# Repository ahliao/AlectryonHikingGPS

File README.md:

Trail Utility Tool

For basic GPS functions when hiking in the middle of nowhere.
Uses a microprocessor for handling GPS data and displaying them to a LCD screen. 

Intended Features:
- Geolocation of module on a geo-image 
- Waypoint management
- Portable battery life of 12 hours
- Rechargable with solar cells
- Rugged package for rough terrain

Possible add-ons:
- Bluetooth support for data recording (or just a SD card)

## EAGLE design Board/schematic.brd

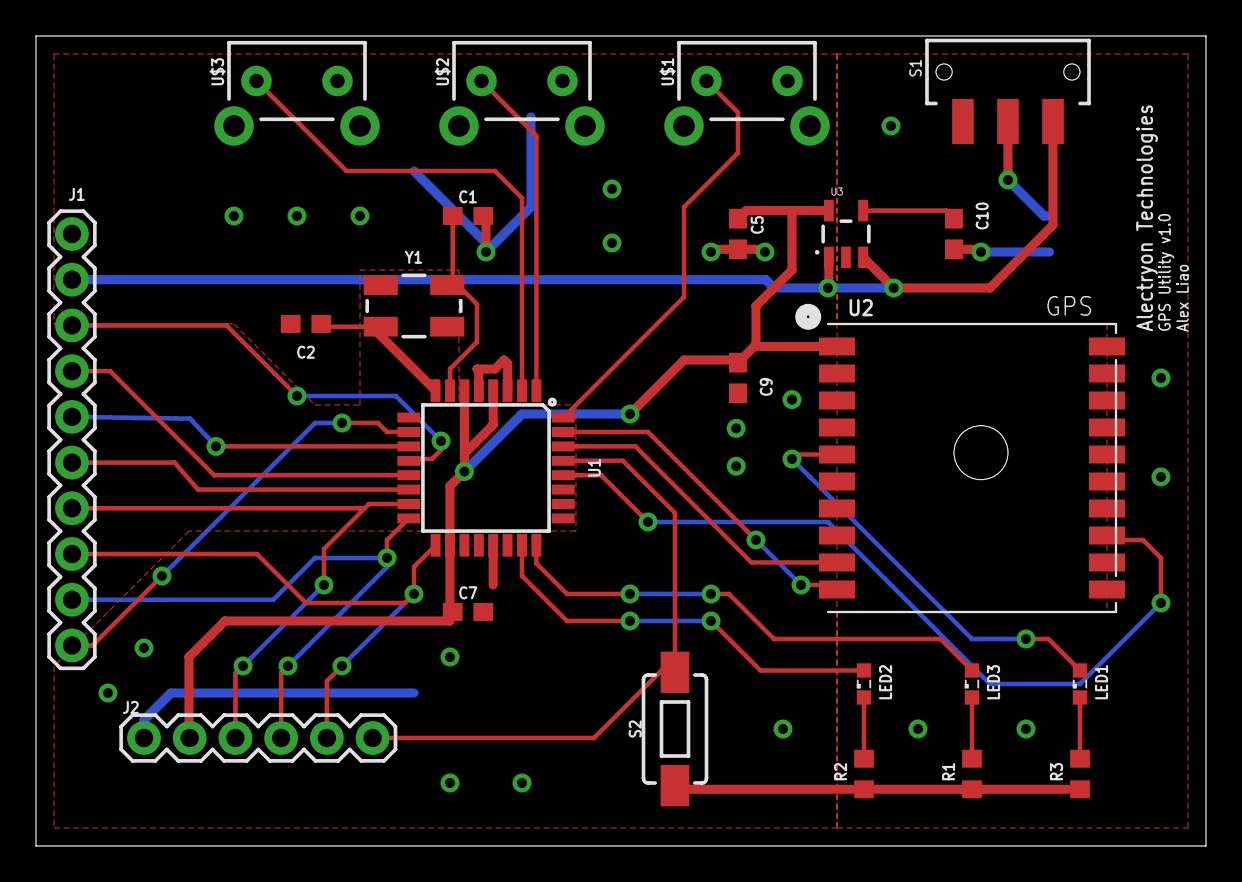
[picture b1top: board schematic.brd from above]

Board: 2 copper layers, 65.0 x 45.0 mm, 24 parts (1 on the bottom side), 28 nets.

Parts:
C1, C2: 22pF; 0603
C5: 10uF; 0603
C7, C9: 0.1uF; 0603
C10: 470pF; 0603
J1: LCD Connector; 1X10
J2: Prog Connector; 1X06
J3: Li-Po Connector; JST-2-SMD
LED1: Red; LED_SML0603
LED2: Green; LED_SML0603
LED3: Blue; LED_SML0603
R1, R2, R3: 470; R0603
S1: PWR Switch; SWITCH_SPDT_SMD
S2: RST Switch; TACTILE_SWITCH_SMD_6.0X3.5MM
U1: ATMEGA328P_TQFP; TQFP32-08
U2: GPS Unit; FGPMMOPA6H
U3: 3.3V/150mA; SOT23-5
U$1, U$2: TACTILE_SWITCH_RIGHT; TACTILE_SWITCH_PTH_RIGHT_ANGLE_KIT
U$3: TACTILE_SWITCH_PTH_RIGHT_ANGLE_KIT
Y1: 16MHz; CRYSTAL-SMD-5X3.2-4PAD

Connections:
BACKLITE: J1.10, U1.10
CARD_CS: J1.5, U1.11
DOWNBTN: U1.2, U$3.2
GND: C1.2, C2.2, C5.2, C7.2, C9.2, C10.2, J1.1, J2.1, J3.1, R1.1, R2.1, R3.2, S2.1, U1.3, U1.5, U1.21, U2.P$3, U2.P$8, U2.P$12, U2.P$19, U3.2, U$1.1, U$2.1, U$3.1
LCDD/C: J1.4, U1.13
LCDRST: J1.3, U1.12
LCD_CS: J1.6, U1.14
LIPO: J3.2, S1.2
MISO: J1.9, J2.4, U1.16
MOSI: J1.7, J2.3, U1.15
unnamed: C1.1, U1.7, Y1.3
unnamed: C2.1, U1.8, Y1.1
unnamed: LED1.C, R3.1
unnamed: C10.1, U3.4
unnamed: LED3.C, R1.2
unnamed: LED2.C, R2.2
unnamed: LED1.A, U2.P$5
PPS: U1.28, U2.P$13
RESET: J2.6, S2.2, U1.29
SCLK: J1.8, J2.5, U1.17
SLEEPBTN: U1.32, U$1.2
STATUS1: LED2.A, U1.23
STATUS2: LED3.A, U1.24
UARTRX: U1.30, U2.P$9
UARTTX: U1.31, U2.P$10
UPBTN: U1.1, U$2.2
VBATT: J1.2, S1.3, U3.1, U3.3
VCC: C5.1, C7.1, C9.1, J2.2, U1.4, U1.6, U1.18, U2.P$1, U3.5

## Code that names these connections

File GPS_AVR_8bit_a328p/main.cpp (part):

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#include "drivers/sd_raw_config.h"

// Define pin outputs
#define LCD_CS 2
#define selectLCD() PORTB &= ~(1 << LCD_CS)
#define unselectLCD() PORTB |= (1 << LCD_CS)
// Status LEDs on PORTC0 and PORTC1
#define STATUS1 0
#define STATUS2 1
#define MENUBTN 2
#define UPBTN 4
#define DOWNBTN 3

// function prototypes
static uint8_t find_file_in_dir(fat_fs_struct* fs, fat_dir_struct* dd, 
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				break;
			case MODE_SCROLLVIEW:
				// Do an overflow counter, if menuBtn held for long
				if (!(PIND & (1 << UPBTN)) && !(PIND & (1 << DOWNBTN))) {
					// Display a menu
					drawMenu();
					menuSelection = MODE_SCROLLVIEW;
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				break;
		}
	}
	if (!(PIND & (1 << UPBTN))) {
		switch (currentMode) {
			case MODE_MENU:
				if (menuSelection > 0) --menuSelection;
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		}
		PORTC &= ~(1 << STATUS1);
	}
	if (!(PIND & (1 << DOWNBTN))) {
		switch (currentMode) {
			case MODE_MENU:
				if (menuSelection < menuSize - 1) ++menuSelection;
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
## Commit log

2017-05-28 Finally using Git
2017-05-28 Added README
2017-05-29 Added active BMP tracking
2017-05-29 Add INT0 interrupt for low power toggle
2017-06-04 PCB v1.0
2017-06-05 Started work on menu
2017-06-08 Added LCD functions + settings menu
2017-06-10 Editted settings menu and added EEPROM to Makefile
2017-06-10 Added Rooster/Alectryon Logo
2017-06-11 Finished About page and tested large image display
2017-06-20 Fixed SRAM crashes

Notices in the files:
parts and their libraries:
SparkFun-Capacitors: Licensing: Creative Commons ShareAlike 4.0 International - https://creativecommons.org/licenses/by-sa/4.0
